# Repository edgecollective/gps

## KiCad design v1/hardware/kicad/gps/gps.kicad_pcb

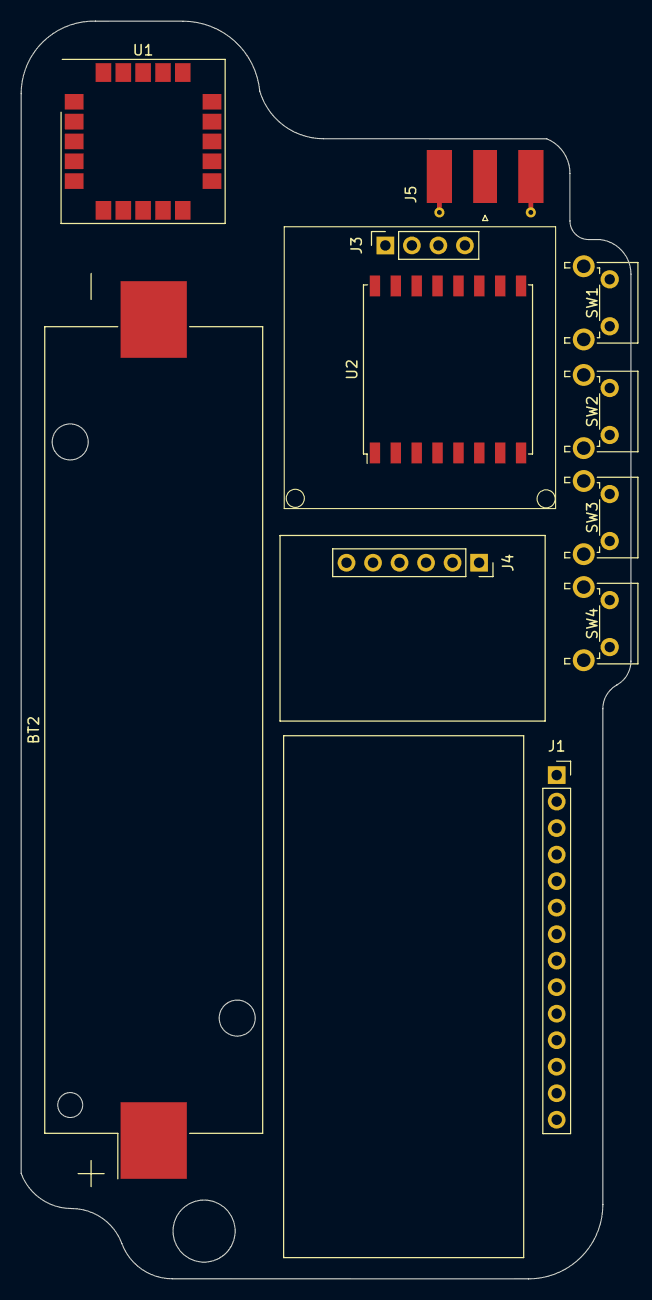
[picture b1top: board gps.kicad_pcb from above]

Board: 2 copper layers, 58.4 x 120.5 mm, 12 parts (1 on the bottom side), 3 nets, no tracks yet.

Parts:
BT1: Battery_Cell; BatteryHolder_Keystone_1058_1x2032
BT2: Battery_Cell; BatteryHolder_Keystone_1042_1x18650
J1: Conn_01x14_Female; PinSocket_1x14_P2.54mm_Vertical
J3: Conn_01x04_Female; PinSocket_1x04_P2.54mm_Vertical
J4: Conn_01x06_Female; PinSocket_1x06_P2.54mm_Vertical
J5: Conn_Coaxial; SMA_Molex_73251-1153_EdgeMount_Horizontal
SW1, SW2, SW3, SW4: SW_Push; SW_Tactile_SPST_Angled_PTS645Vx58-2LFS
U1: ublox_SAM-M8Q
U2: RFM95HW; HOPERF_RFM9XW_SMD

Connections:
3V3: U1.2, U1.17
GND: BT1.2, U1.1, U1.4, U1.5, U1.6, U1.10, U1.11, U1.15, U1.16, U1.20
unnamed: BT1.1, U1.3
